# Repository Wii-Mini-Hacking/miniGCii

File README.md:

# miniGCii
Restore GameCube controller ports to the Wii mini

Designed by @Devnol

This project allows for the readdition of the present but unimplemented GameCube controller ports on the Wii mini motherboard. Ports 1 and 4 are exposed easily as test pads but all 4 gpio lines are present next to the gpu.
The two ports this project readds are exposed through two 3.5mm TRRS jacks coming out the back of the console, right above the USB port.

Pinout is similar to those used by Madmorda or her [GameCube Classic](https://www.youtube.com/watch?v=_BxwS_uTKt4) and Wesk and CrazyGadget on the [GC Nano](https://bitbuilt.net/forums/index.php?threads/gc-nano-the-worlds-smallest-gamecube.5697/):

| Pole | Tip | Ring1 | Ring2 | Sleeve |
| ---- | --- | ----- | ----- | ------ |
| Use  | 5v Rumble | 3.3v | Data | GND |
| Color (inside gcc cable) | White | Green | Red | Blue |

## Project contents

This project consists of all the design files for the trrs jack PCB under [PCB](/PCB)
3D models for mounts will be added later

## LICENSE

This project is licensed under the TAPR Open Hardware License, which can be read [here](LICENSE.txt)

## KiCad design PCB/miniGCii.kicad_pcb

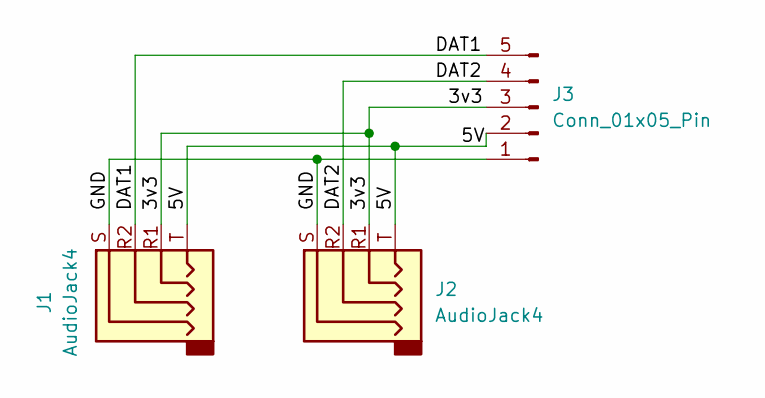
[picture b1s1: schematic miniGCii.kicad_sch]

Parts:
J1, J2: AudioJack4; Jack_3.5mm_KoreanHropartsElec_PJ-320D-4A_Horizontal
J3: Conn_01x05_Pin; JST_PH_S5B-PH-K_1x05_P2.00mm_Horizontal

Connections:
/3v3: J1.R1, J2.R1, J3.3
/5V: J1.T, J2.T, J3.2
/DAT1: J1.R2, J3.5
/DAT2: J2.R2, J3.4
/GND: J1.S, J2.S, J3.1

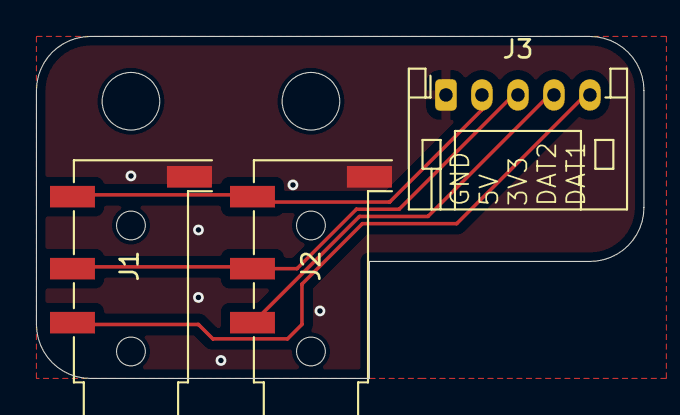
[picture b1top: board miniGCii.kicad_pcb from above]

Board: 2 copper layers, 33.8 x 19.0 mm, 3 parts (0 on the bottom side), 5 nets.

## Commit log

2024-07-01 Added PCB folder, completed schematic
2024-07-01 Populated README
2024-07-01 added license
2024-07-01 Fix pinout table in README.md
2024-07-01 Created PCB layout
2024-07-02 Added silkscreen, resized PCB
2024-07-02 Added pad silks, exported PCB STEP
2024-07-02 changed 3d step to simpler model
2024-07-03 changed connector to 90deg, added fabrication outputs
